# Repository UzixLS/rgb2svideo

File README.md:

## RGB2SVIDEO

This device converts 15KHz RGB + Sync analog video signal to S-Video or CVBS (composite) signal.
Both PAL and NTSC are supported (you should choose one at build).

### Revision C PCB
This PCB is based on AD724 chip and designed to fit into DSUB shell.

[release/pcb.rev.C.pdf](release/pcb.rev.C.pdf) - schematic and bill of materials  
[release/bom_interactive.rev.C.html](https://htmlpreview.github.io/?https://github.com/UzixLS/rgb2svideo/blob/master/release/bom_interactive.rev.C.html) - interactive BOM  
[release/gerber.rev.C.zip](release/gerber.rev.C.zip) - fabrication files  

### Revision A PCB
This PCB is based on BH7236AF/KA2198BD/CXA1645/CXA2075 chips and designed to fit into AK-S-71 shell.

[release/pcb.rev.A2.pdf](release/pcb.rev.A2.pdf) - schematic and bill of materials  
[release/bom_interactive.rev.A2.html](https://htmlpreview.github.io/?https://github.com/UzixLS/rgb2svideo/blob/master/release/bom_interactive.rev.A2.html) - interactive BOM  
[release/gerber.rev.A2.zip](release/gerber.rev.A2.zip) - fabrication files

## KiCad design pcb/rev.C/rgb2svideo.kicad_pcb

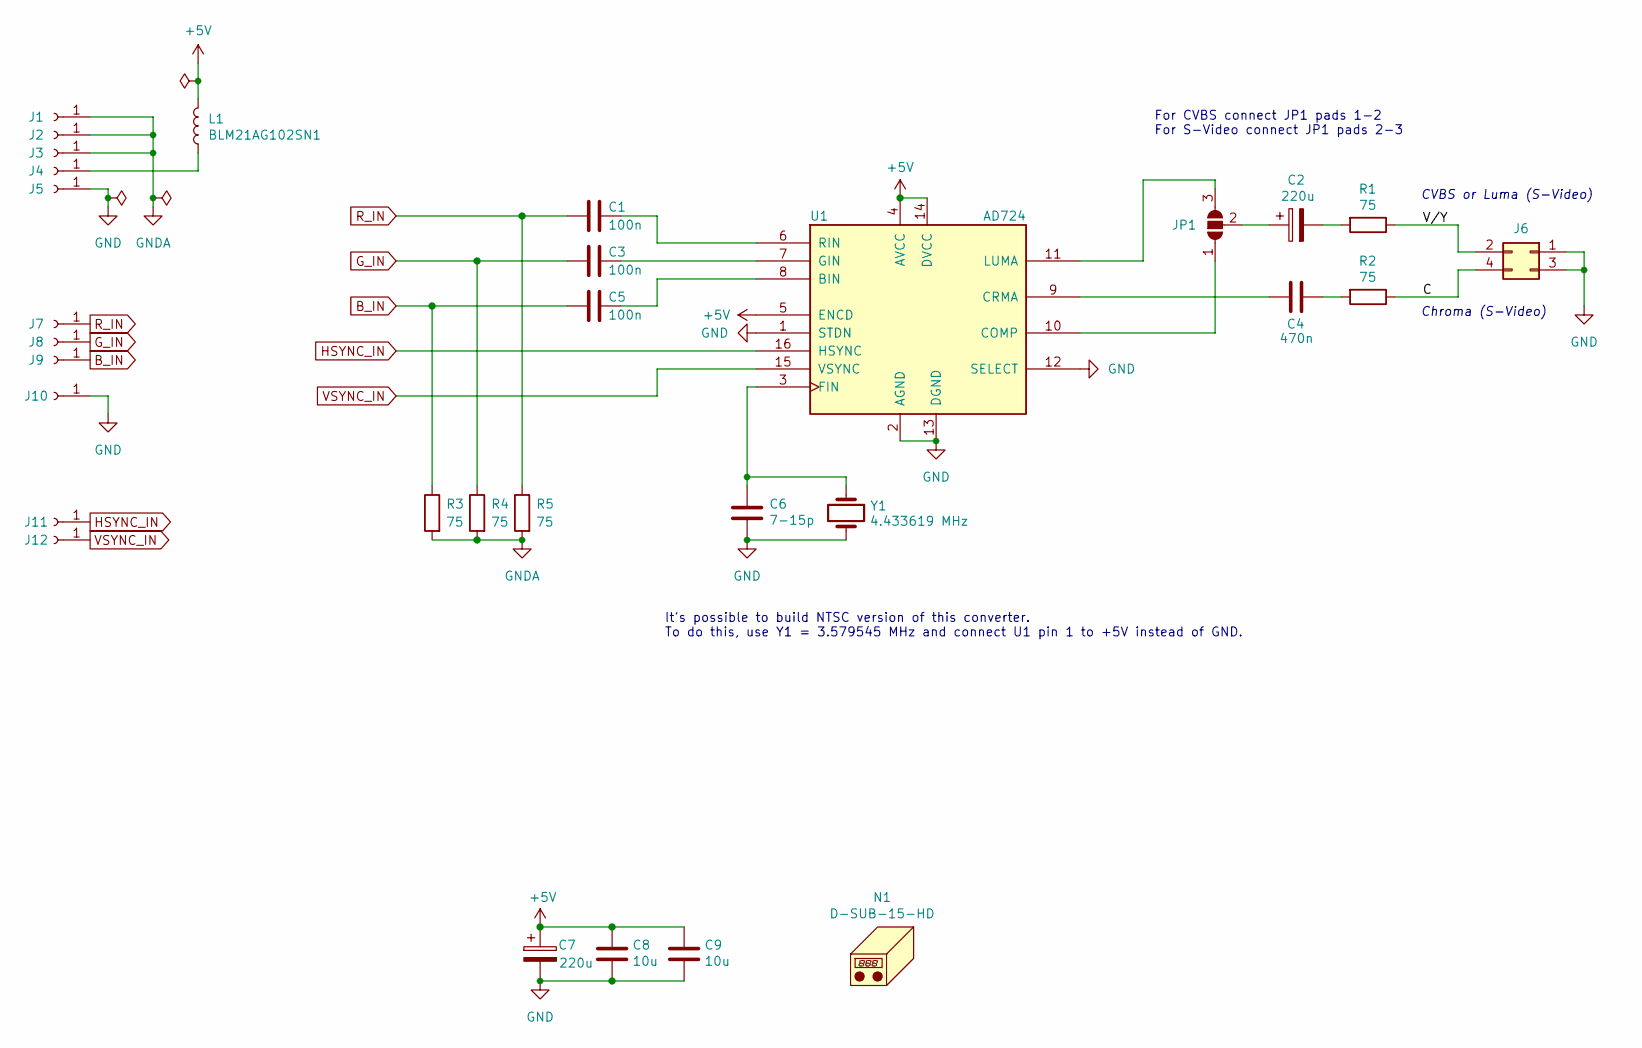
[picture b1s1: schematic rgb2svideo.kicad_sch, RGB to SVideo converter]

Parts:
C1, C3, C5: 100n; C_0603_1608Metric
C2, C7: 220u; CP_EIA-3528-12_Kemet-T
C4: 470n; C_0603_1608Metric
C6: 7-15p; C_0603_1608Metric
C8, C9: 10u; C_0603_1608Metric
J1, J2, J3, J4, J5: Conn_01x01_Socket; TestPoint_Pad_1.5x1.5mm
J6: Conn_02x02_Odd_Even; PinHeader_2x02_P2.54mm_Vertical
J7, J8, J9, J10, J11, J12: Conn_01x01_Socket; TestPoint_Pad_D1.5mm
JP1: SolderJumper_3_Bridged12; SolderJumper-3_P1.3mm_Open_RoundedPad1.0x1.5mm
L1: BLM21AG102SN1; L_0805_2012Metric
N1: D-SUB-15-HD
R1, R2, R3, R4, R5: 75; R_0603_1608Metric
U1: AD724; SOIC-16W_7.5x10.3mm_P1.27mm
Y1: 4.433619 MHz; Crystal_HC49-4H_Vertical

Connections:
+5V: C7.1, C8.1, C9.1, L1.2, U1.4 (AVCC), U1.5 (ENCD), U1.14 (DVCC)
/C: J6.4, R2.1
/V/Y: J6.2, R1.1
B_IN: C5.2, J9.1, R3.1
GND: C6.2, C7.2, C8.2, C9.2, J5.1, J6.1, J6.3, J10.1, U1.1 (STDN), U1.2 (AGND), U1.12 (SELECT), U1.13 (DGND), Y1.2
GNDA: J1.1, J2.1, J3.1, R3.2, R4.2, R5.2
G_IN: C3.2, J8.1, R4.1
HSYNC_IN: J11.1, U1.16 (HSYNC)
unnamed: C2.2, R1.2
unnamed: C4.2, R2.2
unnamed: J4.1, L1.1
unnamed: JP1.1 (A), U1.10 (COMP)
unnamed: JP1.3 (B), U1.11 (LUMA)
unnamed: C2.1, JP1.2 (C)
unnamed: C5.1, U1.8 (BIN)
unnamed: C4.1, U1.9 (CRMA)
unnamed: C6.1, U1.3 (FIN), Y1.1
unnamed: C3.1, U1.7 (GIN)
unnamed: C1.1, U1.6 (RIN)
R_IN: C1.2, J7.1, R5.1
VSYNC_IN: J12.1, U1.15 (VSYNC)

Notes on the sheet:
It's possible to build NTSC version of this converter. To do this, use Y1 = 3.579545 MHz and connect U1 pin 1 to +5V instead of GND.
For CVBS connect JP1 pads 1-2 For S-Video connect JP1 pads 2-3
CVBS or Luma (S-Video)
Chroma (S-Video)

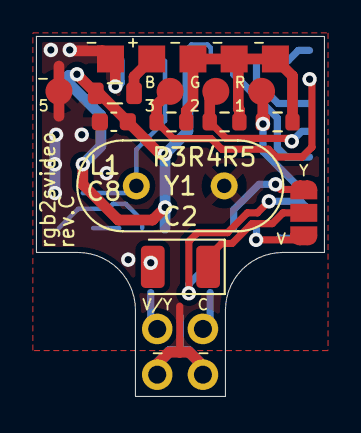
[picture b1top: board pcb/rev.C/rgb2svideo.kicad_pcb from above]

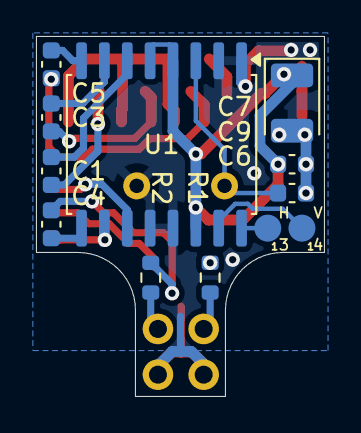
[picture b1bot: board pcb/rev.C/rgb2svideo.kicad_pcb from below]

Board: 2 copper layers, 16.0 x 20.0 mm, 30 parts (12 on the bottom side), 21 nets.

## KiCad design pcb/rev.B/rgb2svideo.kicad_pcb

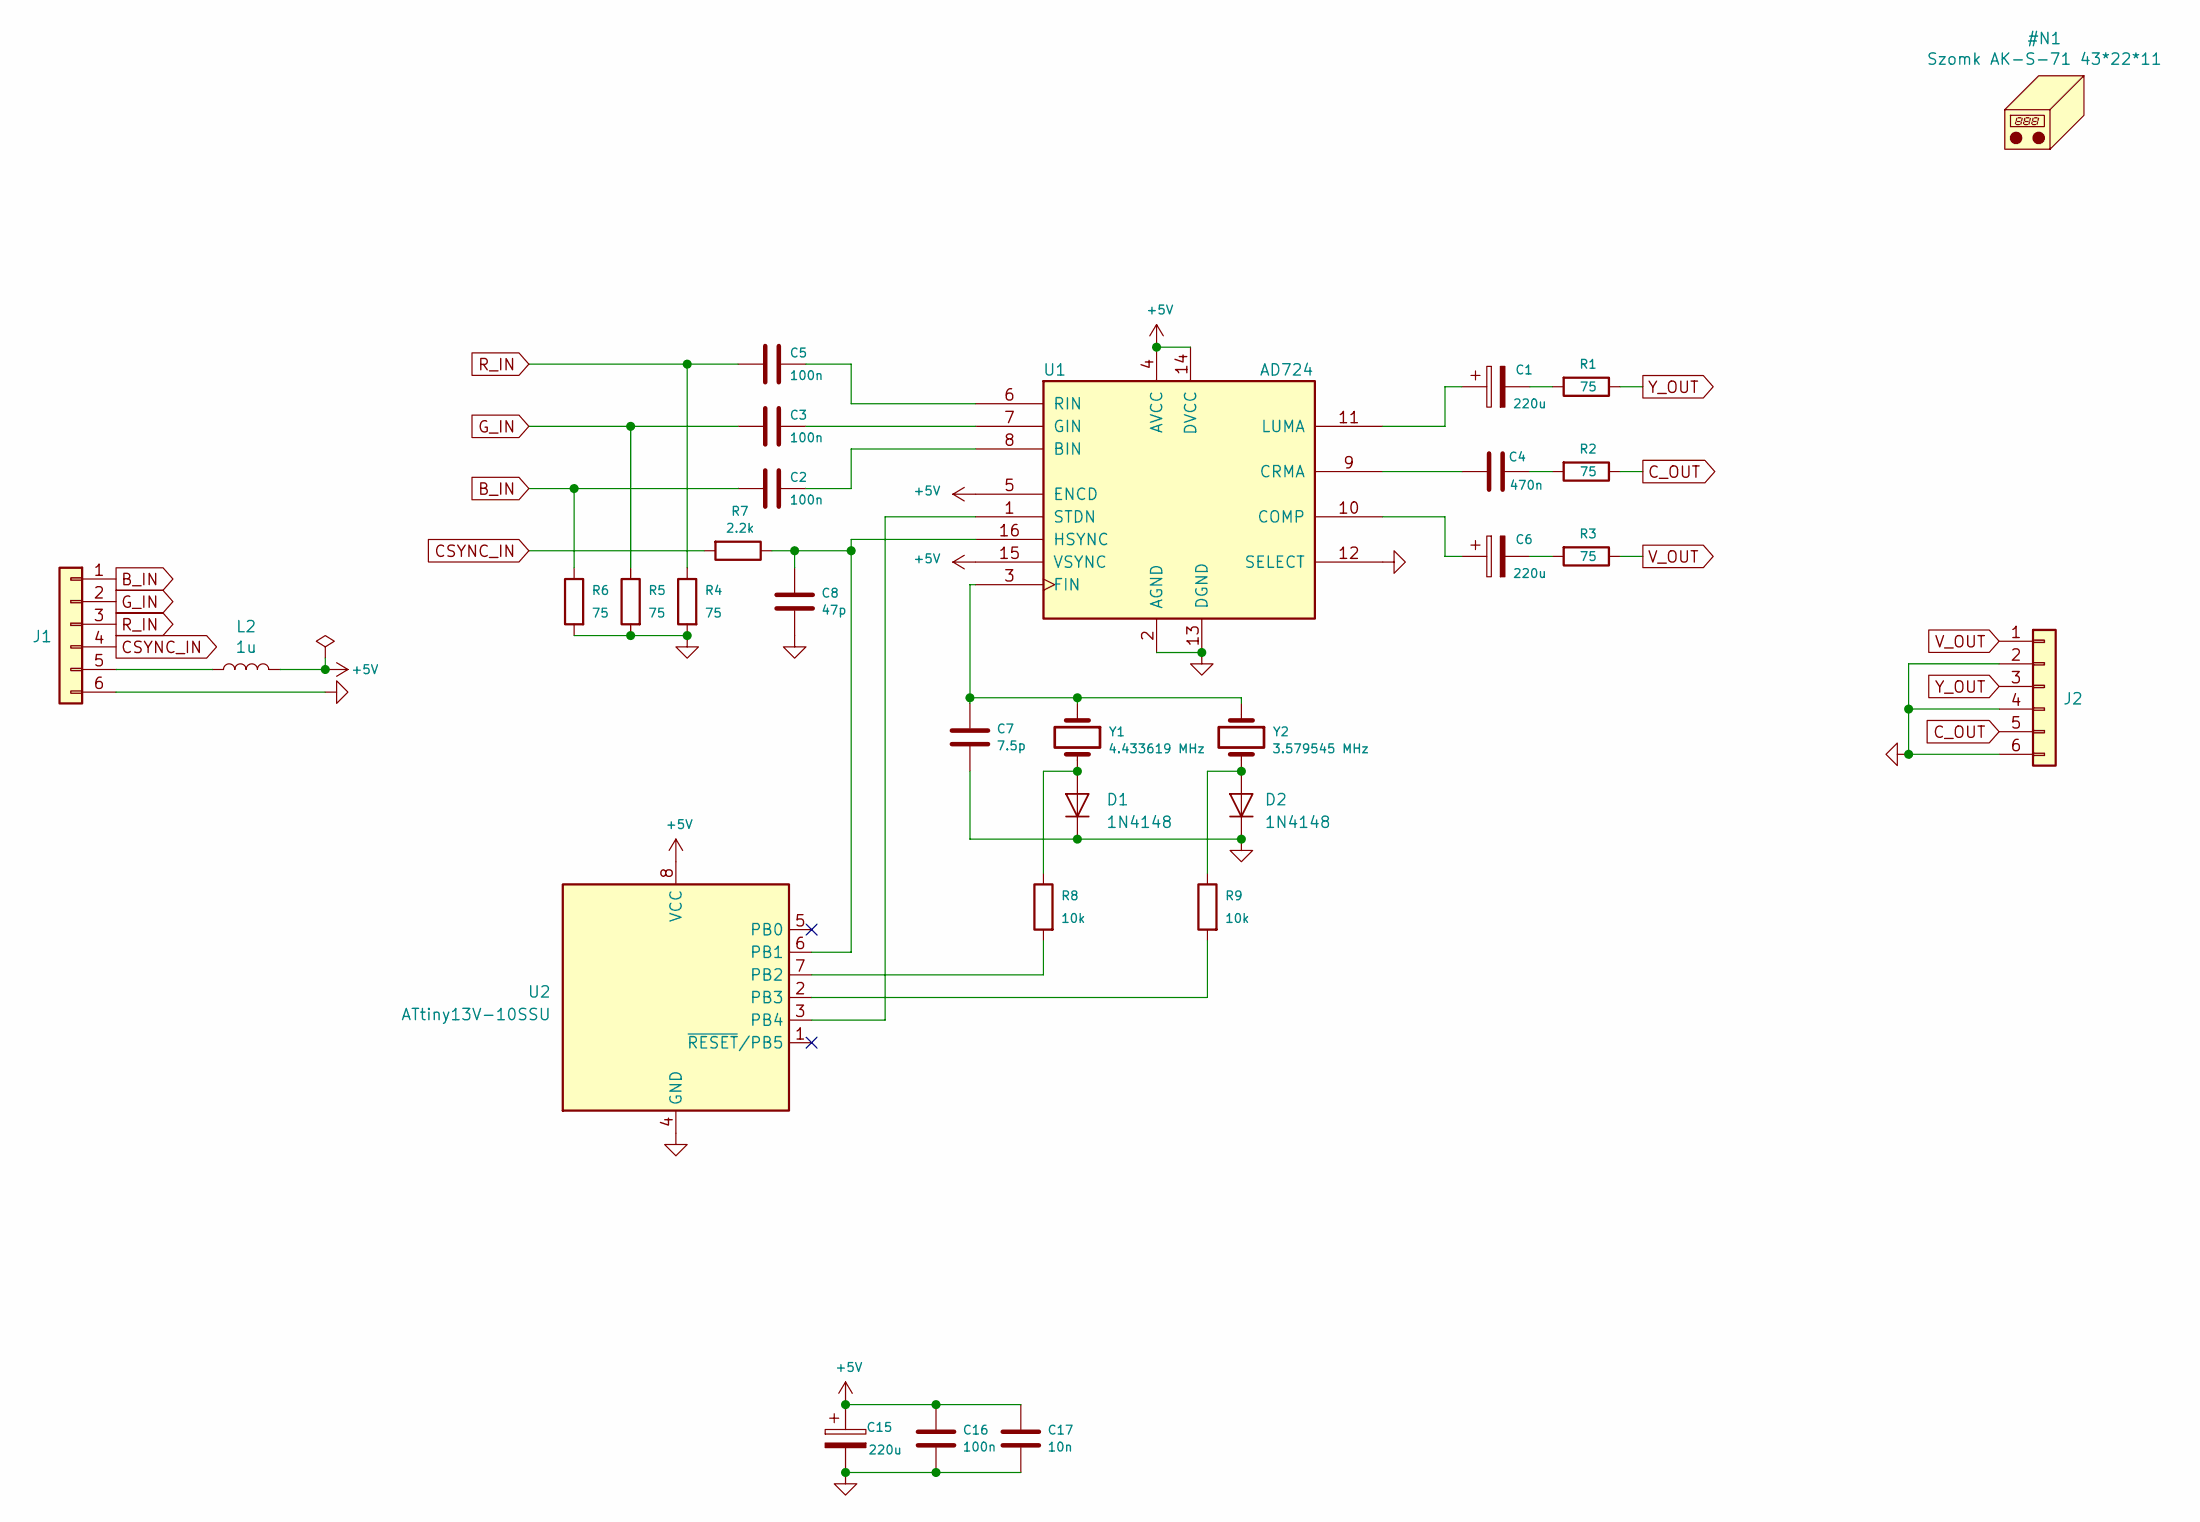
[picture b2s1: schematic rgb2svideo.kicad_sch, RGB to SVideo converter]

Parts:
C1, C6, C15: 220u; CP_EIA-3528-12_Kemet-T
C2, C3, C5: 100n; C_0603_1608Metric_Pad1.08x0.95mm_HandSolder
C4: 470n; C_0805_2012Metric_Pad1.18x1.45mm_HandSolder
C7: 7.5p; C_0603_1608Metric_Pad1.08x0.95mm_HandSolder
C8: 47p; C_0603_1608Metric_Pad1.08x0.95mm_HandSolder
C16: 100n; C_0603_1608Metric_Pad1.05x0.95mm_HandSolder
C17: 10n; C_0603_1608Metric_Pad1.05x0.95mm_HandSolder
D1, D2: 1N4148; D_0805_2012Metric_Pad1.15x1.40mm_HandSolder
J1, J2: Conn_01x06_Odd_Even; PinHeader_1x06_P2.54mm_Vertical
L2: 1u; L_0805_2012Metric_Pad1.15x1.40mm_HandSolder
R1, R2, R3, R4, R5, R6: 75; R_0603_1608Metric_Pad0.98x0.95mm_HandSolder
R7: 2.2k; R_0603_1608Metric_Pad0.98x0.95mm_HandSolder
R8, R9: 10k; R_0603_1608Metric_Pad0.98x0.95mm_HandSolder
U1: AD724; SOIC-16W_7.5x10.3mm_P1.27mm
U2: ATtiny13V-10SSU; SOIC-8_3.9x4.9mm_P1.27mm
Y1: 4.433619 MHz; Crystal_SMD_HC49-SD
Y2: 3.579545 MHz; Crystal_SMD_HC49-SD

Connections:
+5V: C15.1, C16.1, C17.1, L2.2, U1.4 (AVCC), U1.5 (ENCD), U1.14 (DVCC), U1.15 (VSYNC), U2.8 (VCC)
B_IN: C2.2, J1.1, R6.1
CSYNC_IN: J1.4, R7.2
C_OUT: J2.5, R2.1
GND: C7.2, C8.2, C15.2, C16.2, C17.2, D1.1 (K), D2.1 (K), J1.6, J2.2, J2.4, J2.6, R4.2, R5.2, R6.2, U1.2 (AGND), U1.12 (SELECT), U1.13 (DGND), U2.4 (GND)
G_IN: C3.2, J1.2, R5.1
unnamed: C1.1, U1.11 (LUMA)
unnamed: C1.2, R1.2
unnamed: C2.1, U1.8 (BIN)
unnamed: C3.1, U1.7 (GIN)
unnamed: C5.1, U1.6 (RIN)
unnamed: C6.1, U1.10 (COMP)
unnamed: C6.2, R3.2
unnamed: C8.1, R7.1, U1.16 (HSYNC), U2.6 (PB1)
unnamed: J1.5, L2.1
unnamed: C4.2, R2.2
unnamed: R8.2, U2.7 (PB2)
unnamed: R9.2, U2.2 (PB3)
unnamed: U1.1 (STDN), U2.3 (PB4)
unnamed: C7.1, U1.3 (FIN), Y1.1, Y2.1
unnamed: C4.1, U1.9 (CRMA)
unnamed: D1.2 (A), R8.1, Y1.2
unnamed: D2.2 (A), R9.1, Y2.2
R_IN: C5.2, J1.3, R4.1
V_OUT: J2.1, R3.1
Y_OUT: J2.3, R1.1

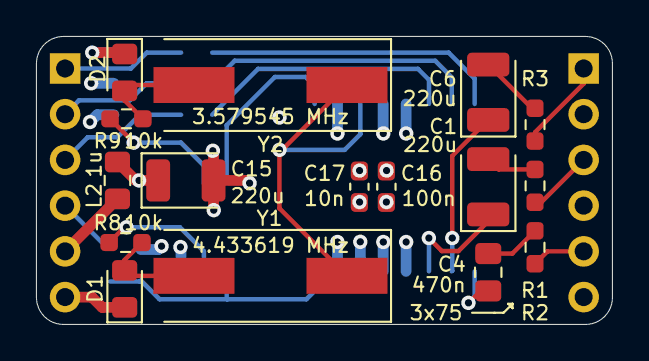
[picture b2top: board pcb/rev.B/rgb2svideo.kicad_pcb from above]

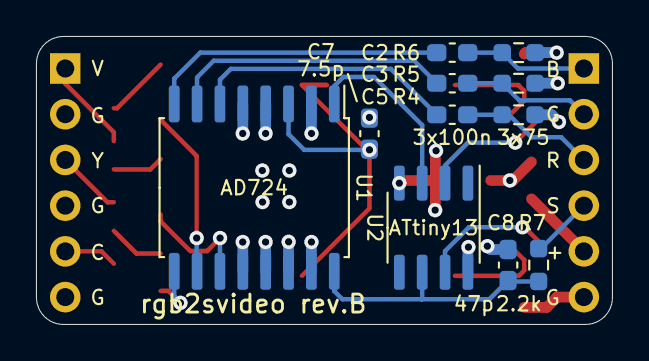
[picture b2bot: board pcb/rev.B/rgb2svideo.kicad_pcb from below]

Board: 4 copper layers, 32.0 x 16.0 mm, 29 parts (11 on the bottom side), 26 nets.

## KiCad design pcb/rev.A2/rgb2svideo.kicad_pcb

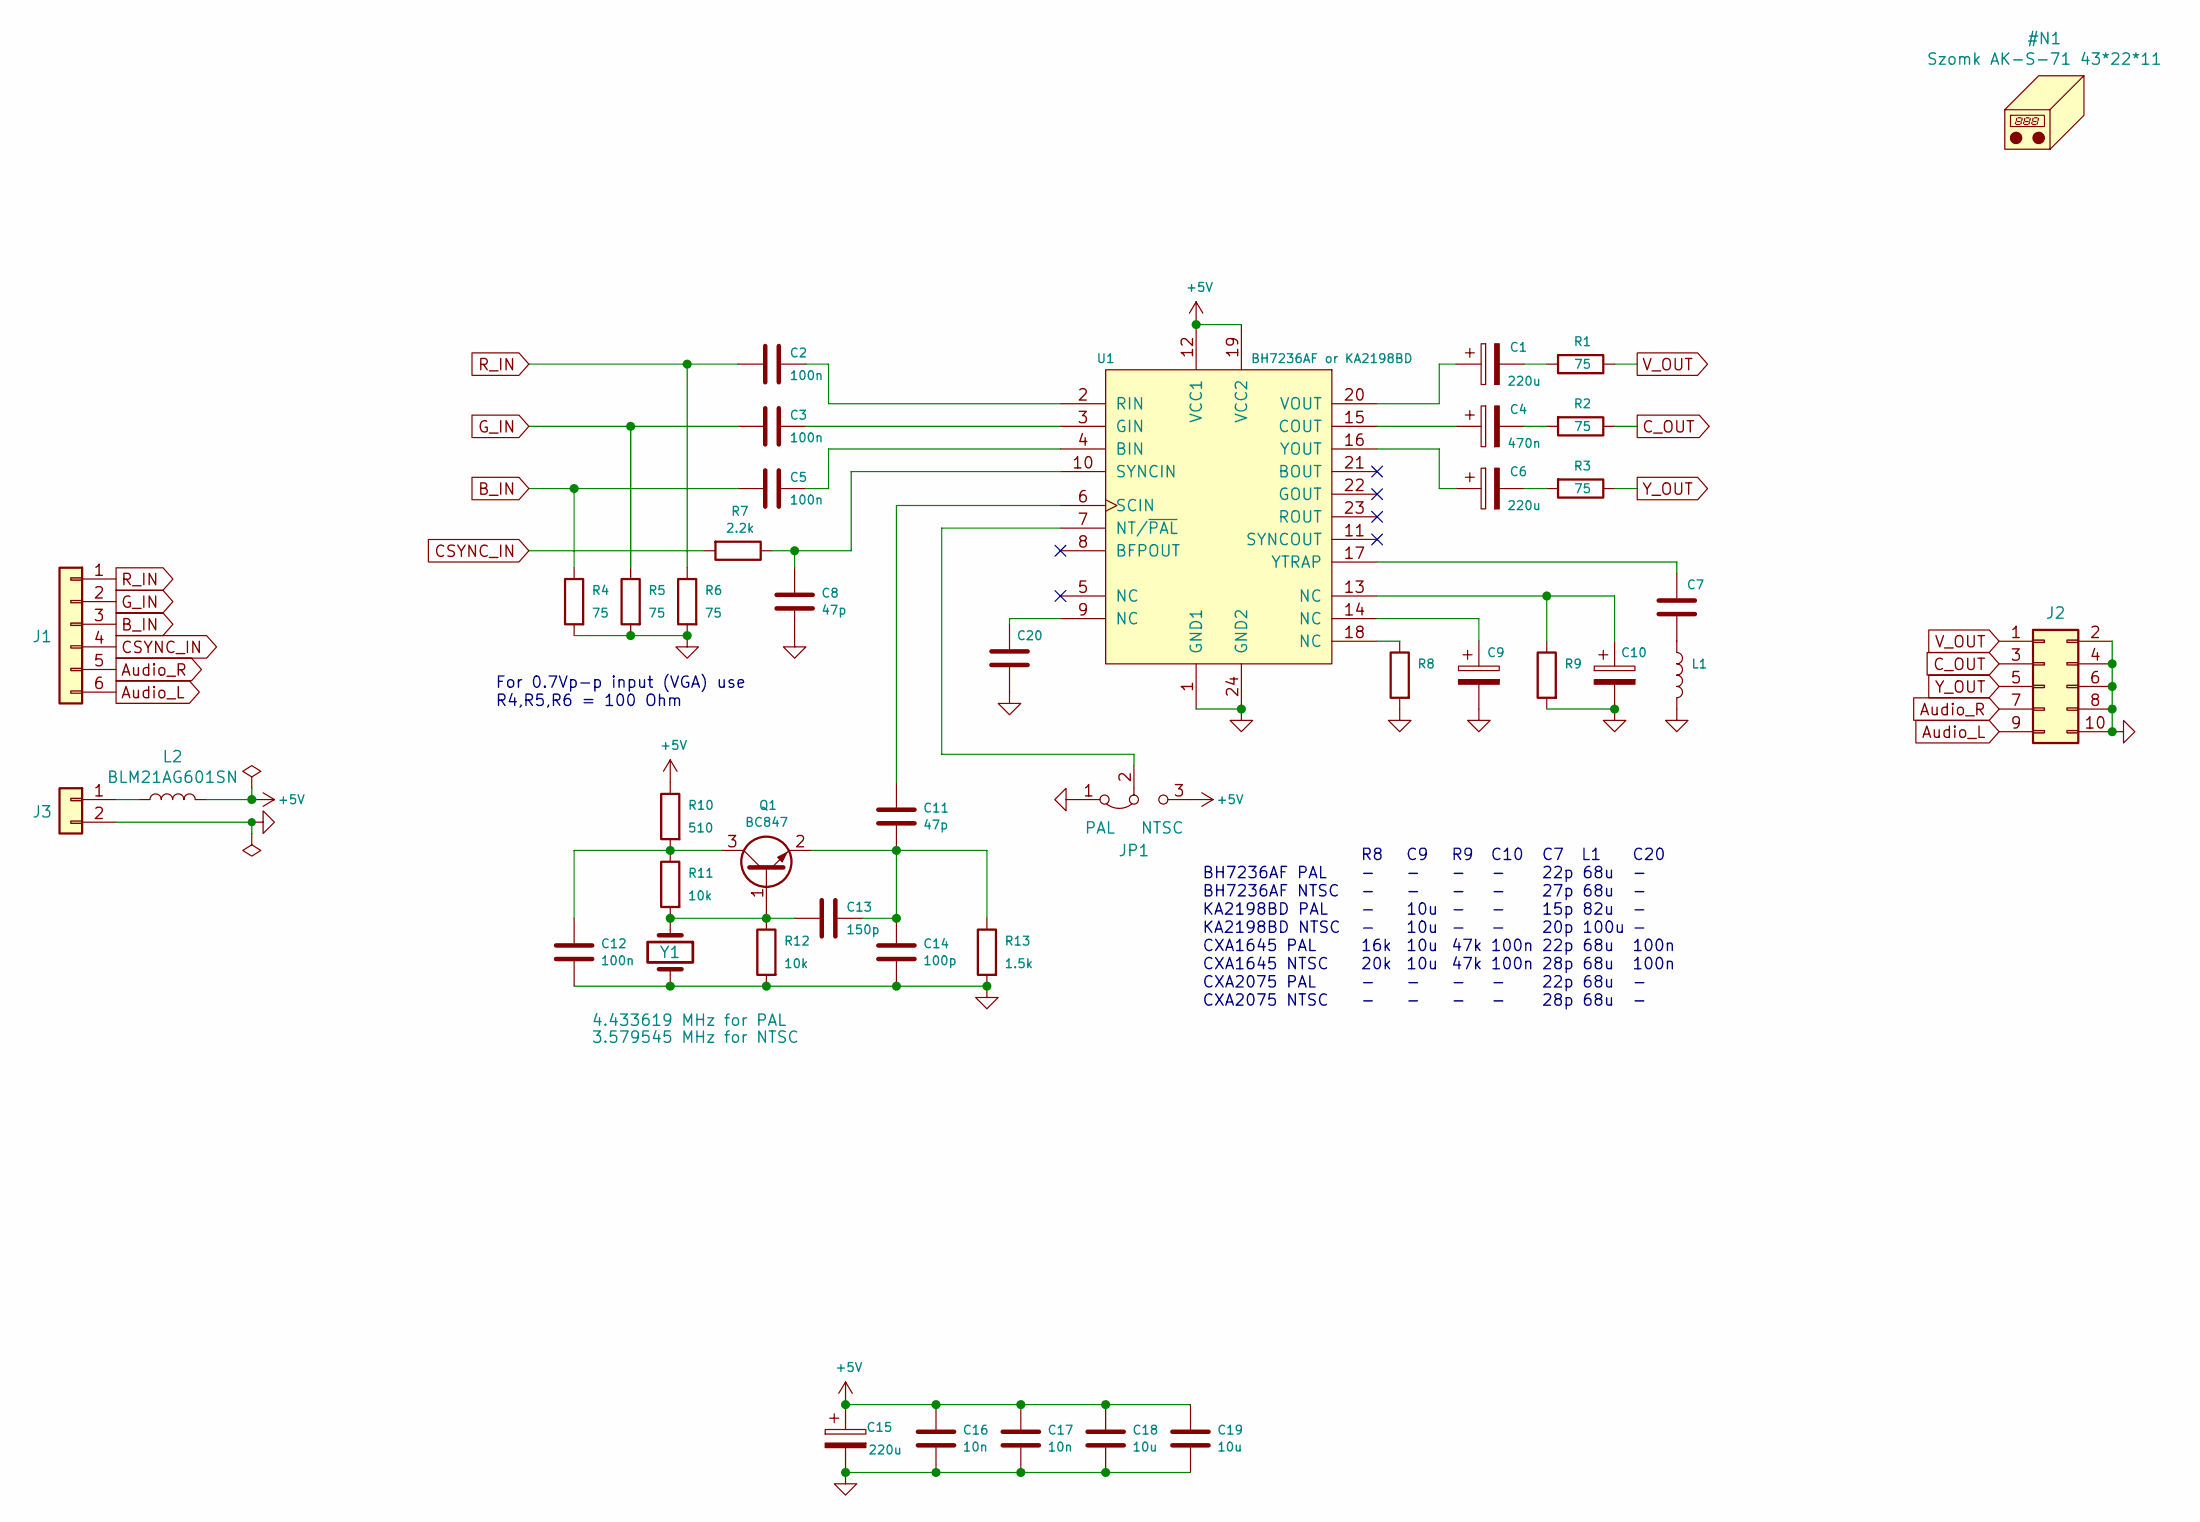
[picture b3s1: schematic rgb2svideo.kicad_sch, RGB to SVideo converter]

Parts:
C1, C6, C15: 220u; CP_EIA-3528-12_Kemet-T
C2, C3, C5, C12: 100n; C_0603_1608Metric_Pad1.08x0.95mm_HandSolder
C4: 470n; C_0603_1608Metric_Pad1.08x0.95mm_HandSolder
C7, C10, C20: *; C_0603_1608Metric_Pad1.08x0.95mm_HandSolder
C8, C11: 47p; C_0603_1608Metric_Pad1.08x0.95mm_HandSolder
C9: *; CP_EIA-3216-18_Kemet-A_Pad1.58x1.35mm_HandSolder
C13: 150p; C_0603_1608Metric_Pad1.08x0.95mm_HandSolder
C14: 100p; C_0603_1608Metric_Pad1.08x0.95mm_HandSolder
C16, C17: 10n; C_0603_1608Metric_Pad1.08x0.95mm_HandSolder
C18, C19: 10u; C_0805_2012Metric_Pad1.18x1.45mm_HandSolder
J1: Conn_01x06_Odd_Even; PinHeader_1x06_P2.54mm_Vertical
J2: Conn_02x05_Odd_Even; PinHeader_2x05_P2.54mm_Vertical
J3: Conn_01x02_Odd_Even; PinHeader_1x02_P2.54mm_Vertical
JP1: Jumper_3_Bridged12; SolderJumper-3_P1.3mm_Bridged12_RoundedPad1.0x1.5mm
L1: *; L_1210_3225Metric_Pad1.42x2.65mm_HandSolder
L2: BLM21AG601SN; L_0805_2012Metric_Pad1.15x1.40mm_HandSolder
Q1: BC847; SOT-23
R1, R2, R3, R4, R5, R6: 75; R_0603_1608Metric_Pad0.98x0.95mm_HandSolder
R7: 2.2k; R_0603_1608Metric_Pad0.98x0.95mm_HandSolder
R8, R9: *; R_0603_1608Metric_Pad0.98x0.95mm_HandSolder
R10: 510; R_0603_1608Metric_Pad0.98x0.95mm_HandSolder
R11, R12: 10k; R_0603_1608Metric_Pad0.98x0.95mm_HandSolder
R13: 1.5k; R_0603_1608Metric_Pad0.98x0.95mm_HandSolder
U1: BH7236AF or KA2198BD; SOP-24_5.0x15.4mm_P1.27mm
Y1: 4.433619MHz; Crystal_HC49-4H_Vertical

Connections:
+5V: C15.1, C16.1, C17.1, C18.1, C19.1, JP1.3 (B), L2.2, R10.1, U1.12 (VCC1), U1.19 (VCC2)
Audio_L: J1.6, J2.9
Audio_R: J1.5, J2.7
B_IN: C5.2, J1.3, R4.1
CSYNC_IN: J1.4, R7.2
C_OUT: J2.3, R2.1
GND: C8.2, C9.2, C10.2, C12.2, C14.2, C15.2, C16.2, C17.2, C18.2, C19.2, C20.1, J2.2, J2.4, J2.6, J2.8, J2.10, J3.2, JP1.1 (A), L1.2, R4.2, R5.2, R6.2, R8.2, R9.2, R12.2, R13.2, U1.1 (GND1), U1.24 (GND2), Y1.2
G_IN: C3.2, J1.2, R5.1
unnamed: C1.1, U1.20 (VOUT)
unnamed: C1.2, R1.2
unnamed: C2.1, U1.2 (RIN)
unnamed: C3.1, U1.3 (GIN)
unnamed: C4.1, U1.15 (COUT)
unnamed: C4.2, R2.2
unnamed: C5.1, U1.4 (BIN)
unnamed: C6.1, U1.16 (YOUT)
unnamed: C6.2, R3.2
unnamed: C7.1, L1.1
unnamed: C7.2, U1.17 (YTRAP)
unnamed: C8.1, R7.1, U1.10 (SYNCIN)
unnamed: C9.1, U1.14 (NC)
unnamed: C10.1, R9.1, U1.13 (NC)
unnamed: C11.1, U1.6 (SCIN)
unnamed: C11.2, C13.1, C14.1, Q1.2 (E), R13.1
unnamed: C12.1, Q1.3 (C), R10.2, R11.1
unnamed: C13.2, Q1.1 (B), R11.2, R12.1, Y1.1
unnamed: J3.1, L2.1
unnamed: JP1.2 (C), U1.7 (NT/~PAL)
unnamed: R8.1, U1.18 (NC)
unnamed: C20.2, U1.9 (NC)
R_IN: C2.2, J1.1, R6.1
V_OUT: J2.1, R1.1
Y_OUT: J2.5, R3.1

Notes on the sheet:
For 0.7Vp-p input (VGA) use R4,R5,R6 = 100 Ohm
C9 - - 10u 10u 10u 10u - -
R8 - - - - 16k 20k - -
R9 C10 - - - - - - - - 47k 100n 47k 100n - - - -
C7 L1 22p 68u 27p 68u 15p 82u 20p 100u 22p 68u 28p 68u 22p 68u 28p 68u
BH7236AF PAL BH7236AF NTSC KA2198BD PAL KA2198BD NTSC CXA1645 PAL CXA1645 NTSC CXA2075 PAL CXA2075 NTSC
C20 - - - - 100n 100n - -

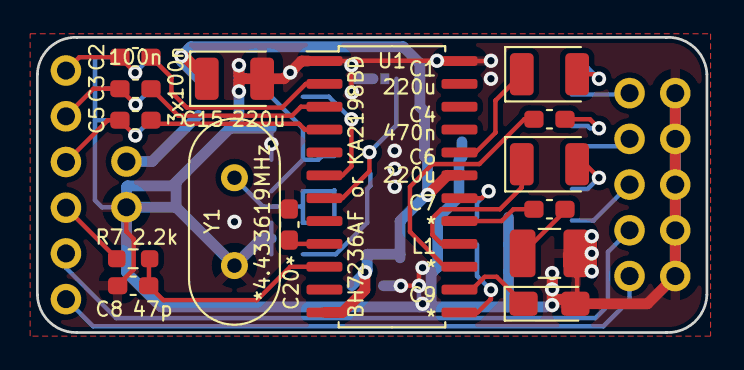
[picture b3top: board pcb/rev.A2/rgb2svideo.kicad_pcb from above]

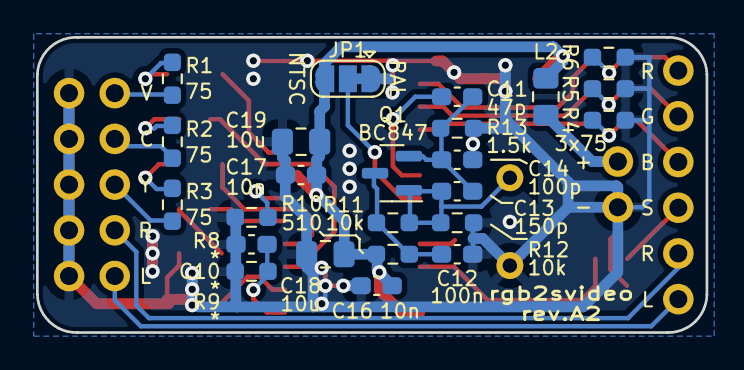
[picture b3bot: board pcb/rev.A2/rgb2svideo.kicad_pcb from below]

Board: 2 copper layers, 37.2 x 16.4 mm, 42 parts (24 on the bottom side), 33 nets.

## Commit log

2021-09-04 initial
2021-09-04 add pcb rev.A
2021-09-04 add gerbers, renders and pdf for rev.A1
2021-09-04 add pcb rev.A1
2021-09-04 add readme
2022-06-19 add license
2022-12-04 add pcb rev.A2
2022-12-04 add gerbers, renders and pdf for rev.A2
2022-12-04 remove gerbers, renders and pdf for rev.A1
2024-11-29 rename out -> release
2024-11-29 add pcb rev.B source files
2024-11-29 add pcb rev.C source files
2024-11-29 add pcb rev.C release files
2026-06-17 remove raw=true from README links
